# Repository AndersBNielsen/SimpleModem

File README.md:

# SimpleModem
Simple Universal Modem

Check out the project on https://hackaday.io/project/186309-simple-universal-modem
Also check out the video demo: https://www.youtube.com/watch?v=k8hlYr6N3Ls

If you are looking for software to use with this, you should check out my 6502 Single Board Computer repo: https://github.com/AndersBNielsen/abn6502

TX:
The component values are configured to expect a 1200/2400Hz FSK modulated square wave on the DataOut(DOut on the silkscreen) pin. This signal is band pass filtered to make a 1V peak to peak sine wave that is output on the ModOut pin.

RX:
The ModIn pin expects an FSK modulated sine wave(Audio). 1V peak to peak recommended input. Output on the DataIn(DIn on the silkscreen) is a 5V square wave that can be used to decode the FSK decoding using an active low interrupt pin. The ModIn pin is not filtered but capacitively coupled using a 100nF cap. It's been tested using computer audio and tape with 1200/2400Hz FSK.

The TRRS jack's poles are meant to be configured using J1-J4 jumpers. An "iPhone" TRRS cable has the pinout right, left, GND, microphone - "Android" TRRS cable usually is right, left, microphone, GND. A standard TRS cable plugged into this would be right, left, GND, GND - for my 1972 tape deck I used a 3.5mm -> RCA/Phono cable and had it configured for ModIn, Modout, GND, GND.

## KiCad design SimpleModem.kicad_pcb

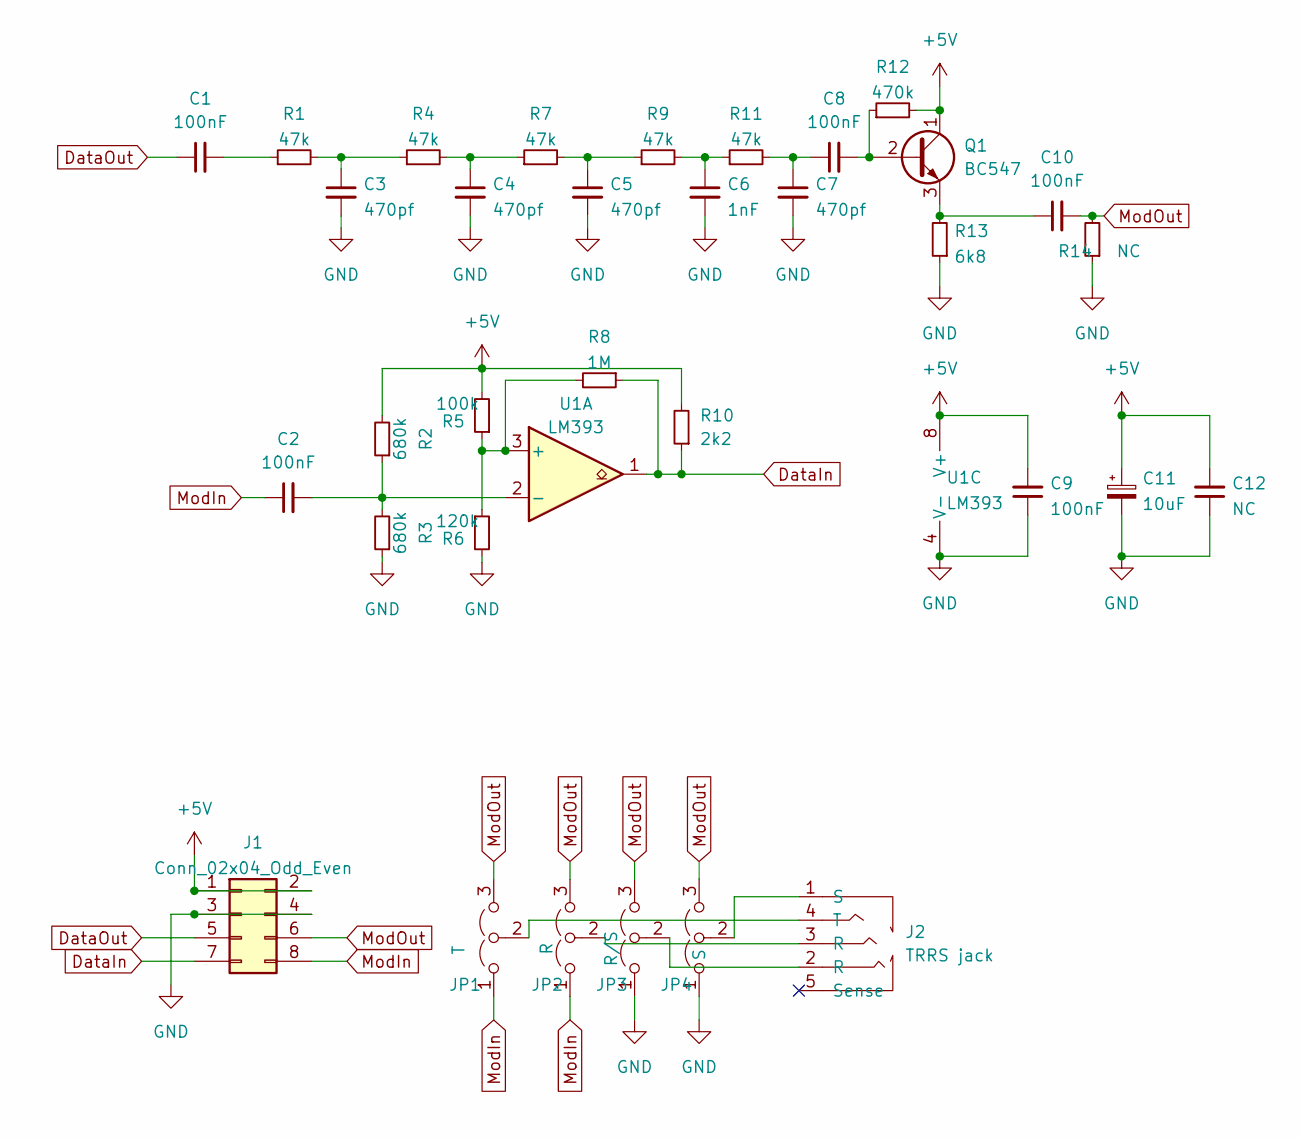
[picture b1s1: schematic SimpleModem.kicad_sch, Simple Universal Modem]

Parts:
C1, C2, C8, C9, C10: 100nF; C_0603_1608Metric
C3, C4, C5, C7: 470pf; C_0805_2012Metric
C6: 1nF; C_0805_2012Metric
C11: 10uF; CP_Elec_4x5.3
C12: NC; C_0805_2012Metric
J1: Conn_02x04_Odd_Even; PinHeader_2x04_P2.54mm_Vertical
J2: TRRS jack; Jack_3.5mm_4Poles_5pins_SMD_ABN
JP1: T; PinHeader_1x03_P2.54mm_Vertical
JP2: R; PinHeader_1x03_P2.54mm_Vertical
JP3: R/S; PinHeader_1x03_P2.54mm_Vertical
JP4: S; PinHeader_1x03_P2.54mm_Vertical
Q1: BC547; TO-92_Inline
R1, R4, R7, R9, R11: 47k; R_0805_2012Metric
R2, R3: 680k; R_0805_2012Metric
R5: 100k; R_0805_2012Metric
R6: 120k; R_0805_2012Metric
R8: 1M; R_0805_2012Metric
R10: 2k2; R_0805_2012Metric
R12: 470k; R_0805_2012Metric
R13: 6k8; R_0805_2012Metric
R14: NC; R_0805_2012Metric
U1: LM393; DIP-8_W7.62mm

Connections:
+5V: C9.2, C11.1, C12.2, J1.1, J1.2, Q1.1 (C), R2.2, R5.2, R10.2, R12.2, U1.8 (V+)
DataIn: J1.7, R8.1, R10.1, U1.1
DataOut: C1.1, J1.5
GND: C3.2, C4.2, C5.2, C6.2, C7.2, C9.1, C11.2, C12.1, J1.3, J1.4, JP3.1 (A), JP4.1 (A), R3.1, R6.2, R13.1, R14.1, U1.4 (V-)
ModIn: C2.1, J1.8, JP1.1 (A), JP2.1 (A)
ModOut: C10.2, J1.6, JP1.3 (B), JP2.3 (B), JP3.3 (B), JP4.3 (B), R14.2
unnamed: C1.2, R1.1
unnamed: C2.2, R2.1, R3.2, U1.2 (-)
unnamed: C3.1, R1.2, R4.1
unnamed: C4.1, R4.2, R7.1
unnamed: C5.1, R7.2, R9.1
unnamed: C6.1, R9.2, R11.1
unnamed: C7.1, C8.1, R11.2
unnamed: C8.2, Q1.2 (B), R12.1
unnamed: C10.1, Q1.3 (E), R13.2
unnamed: J2.1 (S), JP4.2 (C)
unnamed: J2.2 (R), JP3.2 (C)
unnamed: J2.3 (R), JP2.2 (C)
unnamed: J2.4 (T), JP1.2 (C)
unnamed: R5.1, R6.1, R8.2, U1.3 (+)

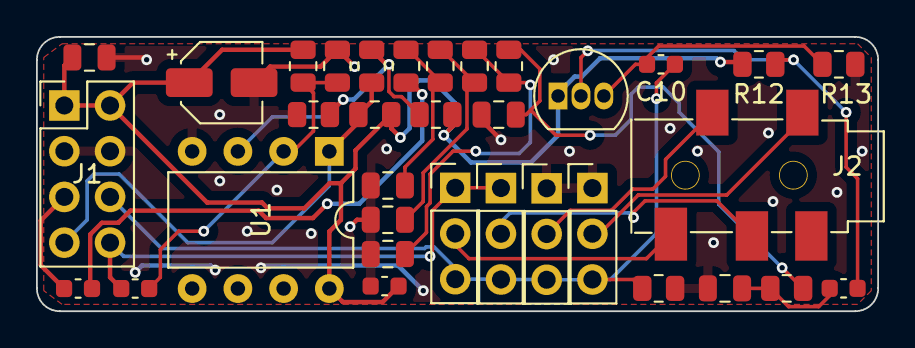
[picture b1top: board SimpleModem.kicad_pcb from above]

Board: 2 copper layers, 46.7 x 15.2 mm, 34 parts (0 on the bottom side), 20 nets.

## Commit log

2022-07-16 Added license
2022-07-16 Initial release
2022-07-16 Gerbers, schematics and screenshots
2022-10-18 Gerbers tested - working as intended
2022-10-18 Photos
2022-10-21 Instructions for connecting and configuring added to ReadMe.

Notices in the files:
SimpleModem.kicad_pcb:
License: Attribution-NonCommercial 4.0 International (CC BY-NC 4.0)
https://creativecommons.org/licenses/by-nc/4.0
SimpleModem.kicad_sch:
Copyright: Anders B. Nielsen
